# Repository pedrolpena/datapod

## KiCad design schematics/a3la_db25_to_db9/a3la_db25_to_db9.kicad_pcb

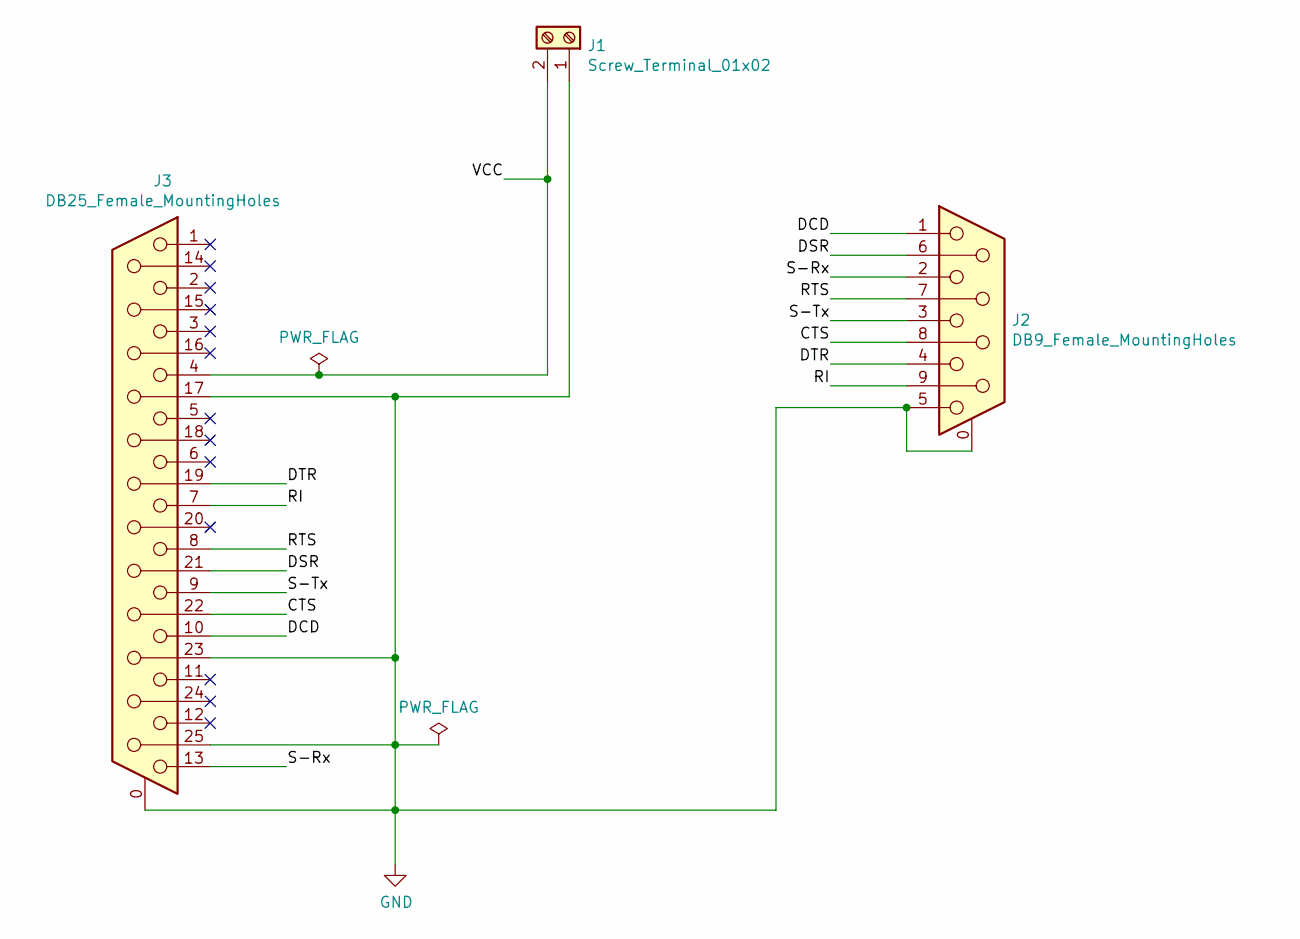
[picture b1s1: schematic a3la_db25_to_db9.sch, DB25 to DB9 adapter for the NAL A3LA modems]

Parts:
J1: Screw_Terminal_01x02; TerminalBlock_Phoenix_PT-1,5-2-5.0-H_1x02_P5.00mm_Horizontal; part# 277-1667-ND
J2: DB9_Female_MountingHoles; DSUB-9_Female_Horizontal_P2.77x2.84mm_EdgePinOffset7.70mm_H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; Part# A32075-ND
J3: DB25_Female_MountingHoles; DSUB-25_Female_Horizontal_P2.77x2.84mm_EdgePinOffset7.70mm_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; Part# A32077-ND

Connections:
/CTS: J2.8, J3.22
/DCD: J2.1, J3.10
/DSR: J2.6, J3.21
/DTR: J2.4, J3.19
/RI: J2.9, J3.7
/RTS: J2.7, J3.8
/S-Rx: J2.2, J3.13
/S-Tx: J2.3, J3.9
/VCC: J1.2, J3.4
GND: J1.1, J2.0 (PAD), J2.5, J3.0 (PAD), J3.17, J3.23, J3.25

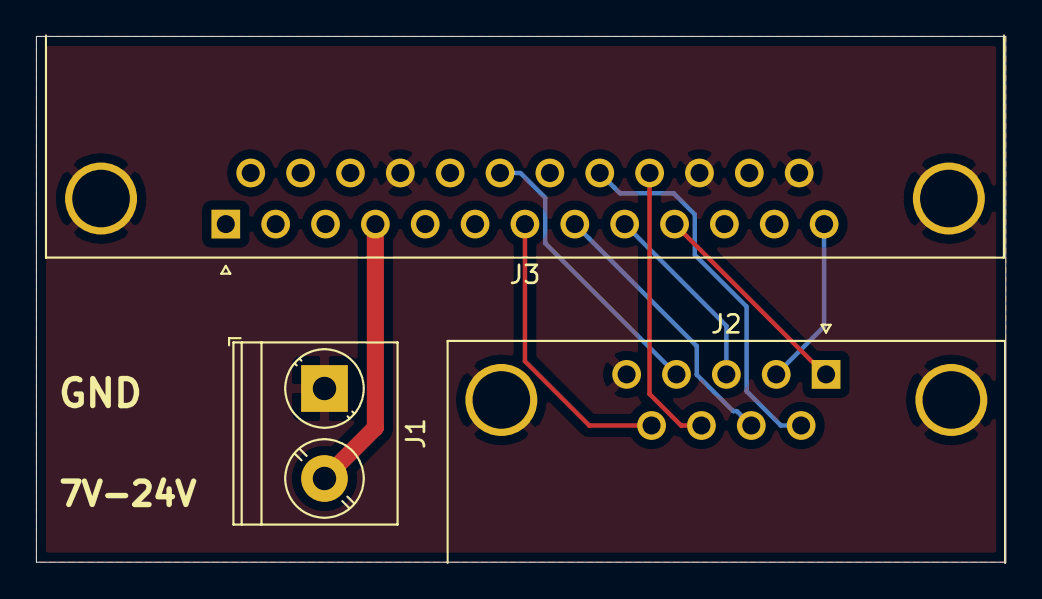
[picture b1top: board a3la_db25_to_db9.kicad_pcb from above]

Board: 2 copper layers, 53.8 x 29.2 mm, 3 parts (0 on the bottom side), 10 nets.

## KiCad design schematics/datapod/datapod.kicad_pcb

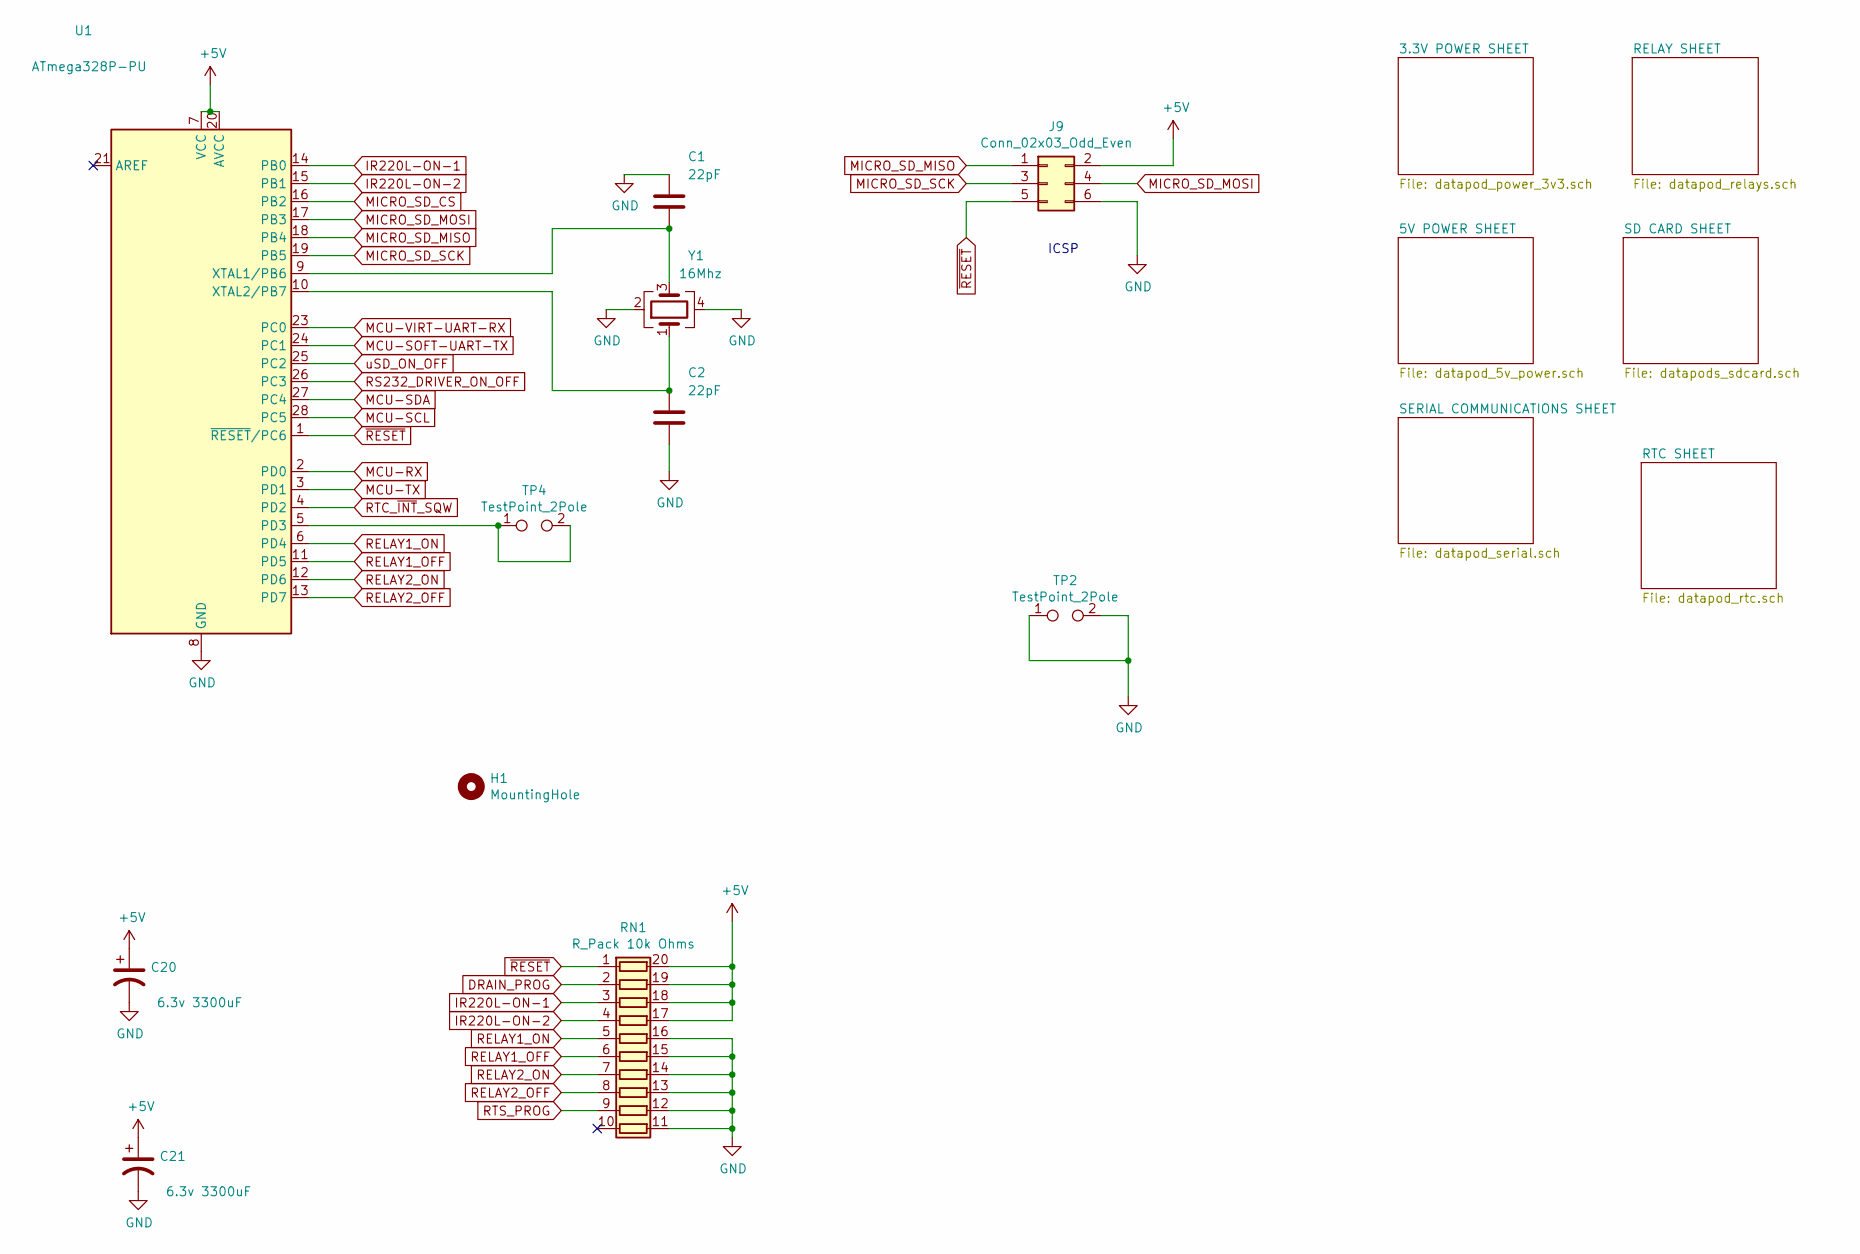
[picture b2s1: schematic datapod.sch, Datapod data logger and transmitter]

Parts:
C1, C2: 22pF; C_1206_3216Metric_Pad1.42x1.75mm_HandSolder; Part# 399-8165-1-ND
C20, C21: 6.3v 3300uF; CP_Radial_D10.0mm_P5.00mm; Part# 493-1009-ND
H1: MountingHole; MountingHole_0.4_inches_Pad_Via; Part# DNI
J9: Conn_02x03_Odd_Even; PinHeader_2x03_P2.54mm_Vertical_SMD; Part# WM17457-ND
RN1: R_Pack 10k Ohms; SSOP-20_3.9x8.7mm_P0.635mm; Part# OSOPT-10KACT-ND
TP2, TP4: TestPoint_2Pole; TestPoint_2Pads_Pitch5.08mm_Drill1.3mm; Part# DNI
U1: ATmega328P-PU; DIP-28_W7.62mm_SMDSocket_SmallPads; Part# 110-47-328-41-105000
Y1: 16Mhz; Oscillator_SMD_EuroQuartz_XO32-4Pin_3.2x2.5mm_HandSoldering; Part# 732-FA-23816B-C

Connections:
+5V: C20.1, C21.1, J9.2, RN1.17 (R4.2), RN1.18 (R3.2), RN1.19 (R2.2), RN1.20 (R1.2), U1.7 (VCC), U1.20 (AVCC); also elsewhere on the board
DRAIN_PROG: RN1.2 (R2.1); also elsewhere on the board
GND: C1.1, C2.2, C20.2, C21.2, J9.6, RN1.11 (R10.2), RN1.12 (R9.2), RN1.13 (R8.2), RN1.14 (R7.2), RN1.15 (R6.2), RN1.16 (R5.2), TP2.1, TP2.2, U1.8 (GND), U1.22 (GND), Y1.2, Y1.4; also elsewhere on the board
IR220L-ON-1: RN1.3 (R3.1), U1.14 (PB0); also elsewhere on the board
IR220L-ON-2: RN1.4 (R4.1), U1.15 (PB1); also elsewhere on the board
MCU-RX: U1.2 (PD0); also elsewhere on the board
MCU-SCL: U1.28 (PC5); also elsewhere on the board
MCU-SDA: U1.27 (PC4); also elsewhere on the board
MCU-SOFT-UART-TX: U1.24 (PC1); also elsewhere on the board
MCU-TX: U1.3 (PD1); also elsewhere on the board
MCU-VIRT-UART-RX: U1.23 (PC0); also elsewhere on the board
MICRO_SD_CS: U1.16 (PB2); also elsewhere on the board
MICRO_SD_MISO: J9.1, U1.18 (PB4); also elsewhere on the board
MICRO_SD_MOSI: J9.4, U1.17 (PB3); also elsewhere on the board
MICRO_SD_SCK: J9.3, U1.19 (PB5); also elsewhere on the board
unnamed: C1.2, U1.9 (XTAL1/PB6), Y1.3
unnamed: C2.1, U1.10 (XTAL2/PB7), Y1.1
unnamed: TP4.1, TP4.2, U1.5 (PD3)
RELAY1_OFF: RN1.6 (R6.1), U1.11 (PD5); also elsewhere on the board
RELAY1_ON: RN1.5 (R5.1), U1.6 (PD4); also elsewhere on the board
RELAY2_OFF: RN1.8 (R8.1), U1.13 (PD7); also elsewhere on the board
RELAY2_ON: RN1.7 (R7.1), U1.12 (PD6); also elsewhere on the board
RS232_DRIVER_ON_OFF: U1.26 (PC3); also elsewhere on the board
RTC_~INT~_SQW: U1.4 (PD2); also elsewhere on the board
RTS_PROG: RN1.9 (R9.1); also elsewhere on the board
uSD_ON_OFF: U1.25 (PC2); also elsewhere on the board
~RESET: J9.5, RN1.1 (R1.1), U1.1 (~RESET~/PC6); also elsewhere on the board

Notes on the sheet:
ICSP

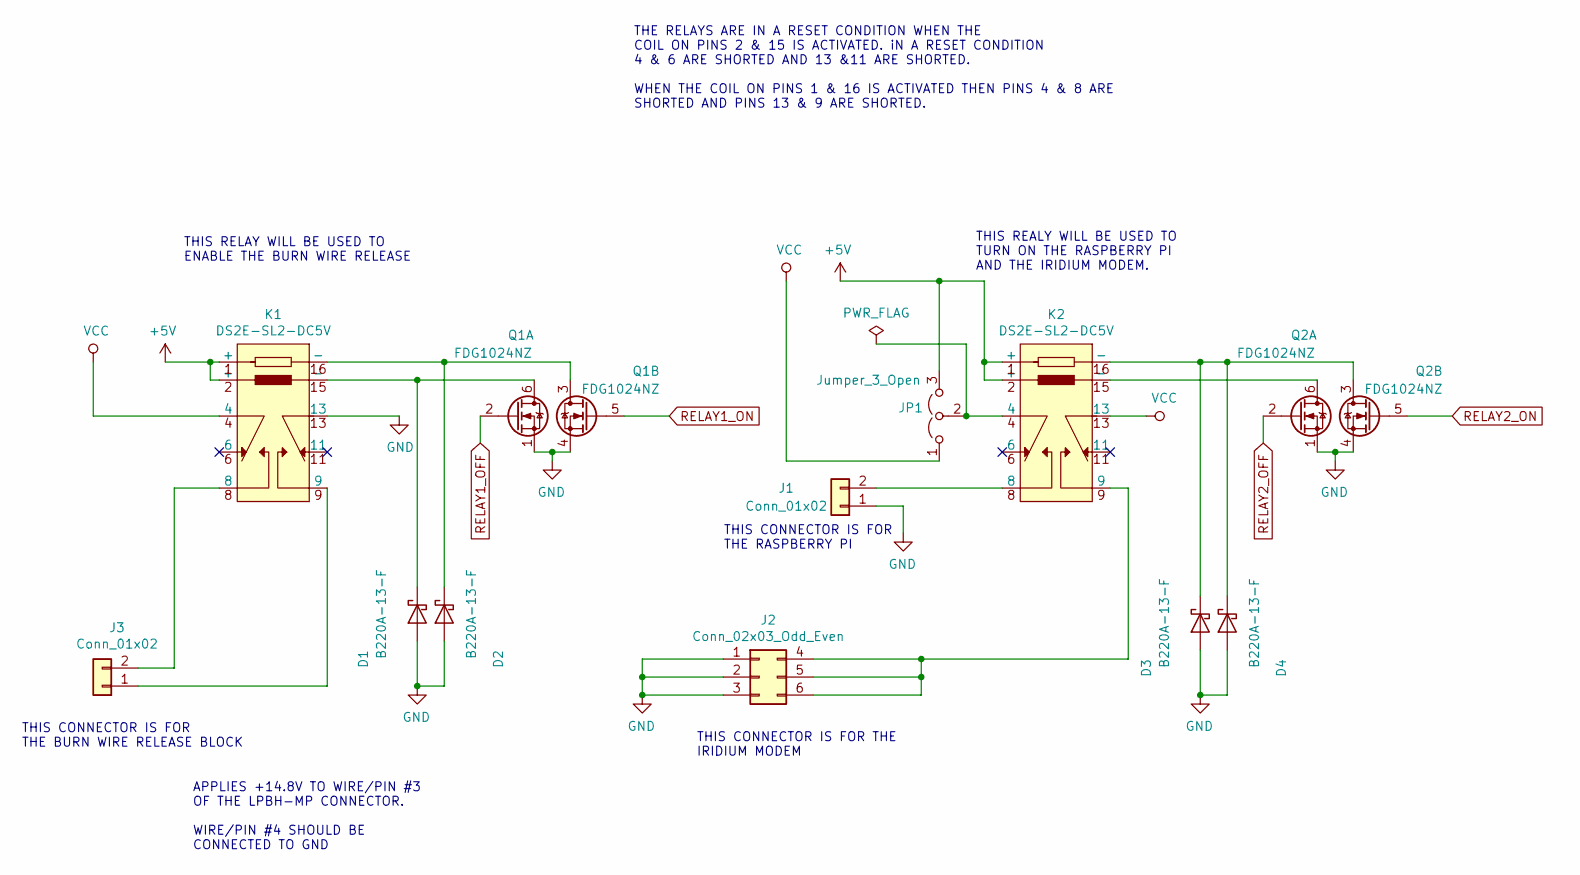
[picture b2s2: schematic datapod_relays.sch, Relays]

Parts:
D1, D2, D3, D4: B220A-13-F; D_SMA; Part# B220A-FDIDKR-ND
J1: Conn_01x02; Molex_Mini-Fit_Jr_5569-02A1_2x01_P4.20mm_Horizontal; Part# WM3900-ND
J2: Conn_02x03_Odd_Even; Molex_Mega-Fit_76825-0006_2x03_P5.70mm_Horizontal; Part# WM11971-ND
J3: Conn_01x02; Molex_Mega-Fit_76825-0002_2x01_P5.70mm_Horizontal; Part# WM11969-ND
JP1: Jumper_3_Open; SolderJumper-3_P1.3mm_Open_RoundedPad1.0x1.5mm
K1, K2: DS2E-SL2-DC5V; DIP-16_W7.62mm_SMDSocket_SmallPads; Part# ED11086-ND
Q1, Q2: FDG1024NZ; SOT-363_SC-70-6; Part# FDG1024NZFSCT-ND

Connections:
+5V: JP1.3 (B), K1.1 (+), K1.2 (+), K2.1 (+), K2.2 (+); also elsewhere on the board
GND: D1.2 (A), D2.2 (A), D3.2 (A), D4.2 (A), J1.1, J2.1, J2.2, J2.3, K1.13, Q1.1 (S), Q1.4 (S), Q2.1 (S), Q2.4 (S); also elsewhere on the board
unnamed: D1.1 (K), K1.15 (-), Q1.6 (D)
unnamed: D2.1 (K), K1.16 (-), Q1.3 (D)
unnamed: D3.1 (K), D4.1 (K), K2.16 (-), Q2.3 (D)
unnamed: J1.2, K2.8
unnamed: J2.4, J2.5, J2.6, K2.9
unnamed: J3.1, K1.9
unnamed: J3.2, K1.8
unnamed: JP1.2 (C), K2.4
unnamed: K2.15 (-), Q2.6 (D)
RELAY1_OFF: Q1.2 (G); also elsewhere on the board
RELAY1_ON: Q1.5 (G); also elsewhere on the board
RELAY2_OFF: Q2.2 (G); also elsewhere on the board
RELAY2_ON: Q2.5 (G); also elsewhere on the board

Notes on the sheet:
THE RELAYS ARE IN A RESET CONDITION WHEN THE COIL ON PINS 2 & 15 IS ACTIVATED. iN A RESET CONDITION 4 & 6 ARE SHORTED AND 13 &11 ARE SHORTED. WHEN THE COIL ON PINS 1 & 16 IS ACTIVATED THEN PINS 4 & 8 ARE SHORTED AND PINS 13 & 9 ARE SHORTED.
THIS RELAY WILL BE USED TO ENABLE THE BURN WIRE RELEASE
THIS REALY WILL BE USED TO TURN ON THE RASPBERRY PI AND THE IRIDIUM MODEM.
APPLIES +14.8V TO WIRE/PIN #3 OF THE LPBH-MP CONNECTOR. WIRE/PIN #4 SHOULD BE CONNECTED TO GND
THIS CONNECTOR IS FOR THE IRIDIUM MODEM
THIS CONNECTOR IS FOR THE BURN WIRE RELEASE BLOCK
THIS CONNECTOR IS FOR THE RASPBERRY PI

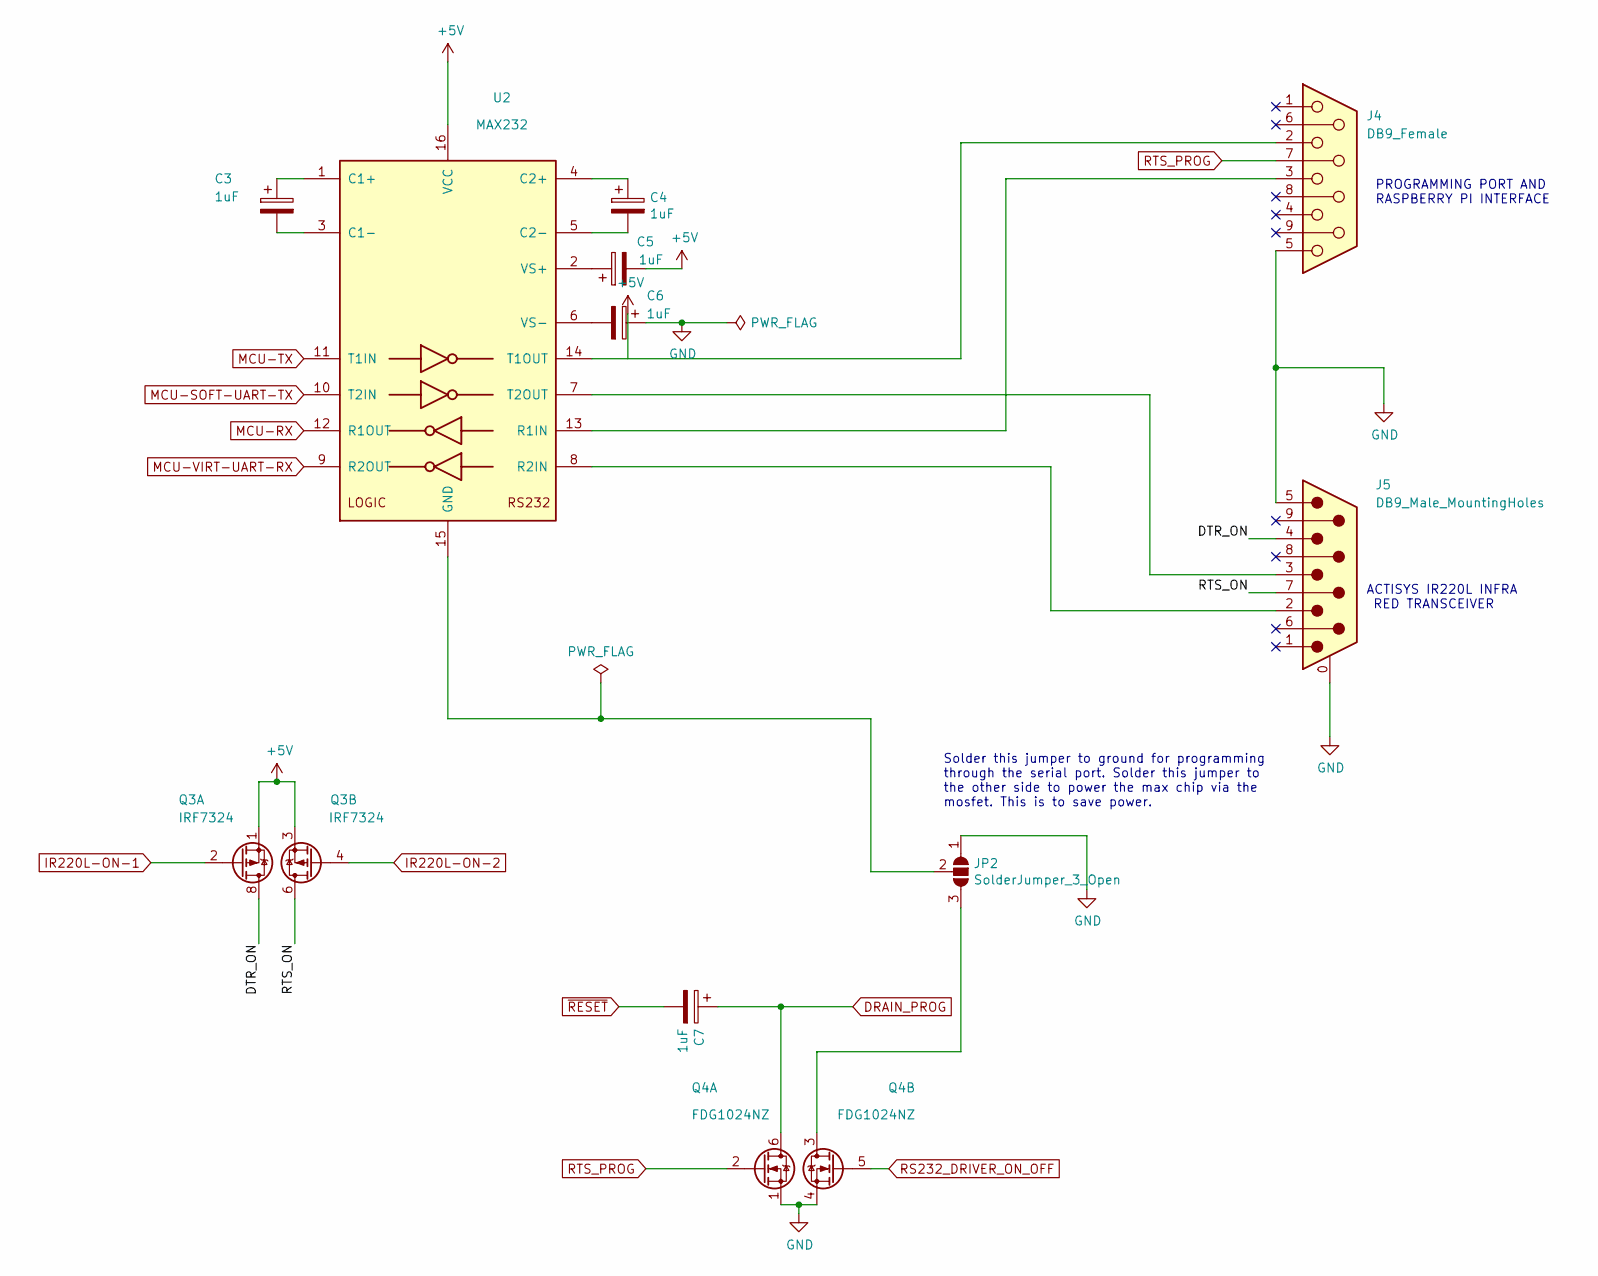
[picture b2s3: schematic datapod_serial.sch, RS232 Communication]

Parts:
C3, C4, C5, C6, C7: 1uF; C_0805_2012Metric_Pad1.15x1.40mm_HandSolder; Part# TCJP105M025R0500
J4: DB9_Female; DSUB-9_Female_Horizontal_P2.77x2.84mm_EdgePinOffset7.70mm_H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; Part# AE10921-ND
J5: DB9_Male_MountingHoles; DSUB-9_Male_Horizontal_P2.77x2.84mm_EdgePinOffset7.70mm_Hou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; Part# AE10968-ND
JP2: SolderJumper_3_Open; SolderJumper-3_P1.3mm_Open_RoundedPad1.0x1.5mm; Part# DNI
Q3: IRF7324; SOIC-8_3.9x4.9mm_P1.27mm; Part# IRF7324PBFTR-ND
Q4: FDG1024NZ; SOT-363_SC-70-6; Part# FDG1024NZFSCT-ND
U2: MAX232; SOIC-16_3.9x9.9mm_P1.27mm; Part# 296-14619-1-ND

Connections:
+5V: C5.2, Q3.1 (S1), Q3.3 (S2), U2.16 (VCC); also elsewhere on the board
/SERIAL COMMUNICATIONS SHEET/DTR_ON: J5.4, Q3.7 (D1), Q3.8 (D1)
/SERIAL COMMUNICATIONS SHEET/RTS_ON: J5.7, Q3.5 (D2), Q3.6 (D2)
DRAIN_PROG: C7.1, Q4.6 (D); also elsewhere on the board
GND: C6.1, J4.5, J5.0 (PAD), J5.5, JP2.1 (A), Q4.1 (S), Q4.4 (S); also elsewhere on the board
IR220L-ON-1: Q3.2 (G1); also elsewhere on the board
IR220L-ON-2: Q3.4 (G2); also elsewhere on the board
MCU-RX: U2.12 (R1OUT); also elsewhere on the board
MCU-SOFT-UART-TX: U2.10 (T2IN); also elsewhere on the board
MCU-TX: U2.11 (T1IN); also elsewhere on the board
MCU-VIRT-UART-RX: U2.9 (R2OUT); also elsewhere on the board
unnamed: C3.1, U2.1 (C1+)
unnamed: C3.2, U2.3 (C1-)
unnamed: C4.1, U2.4 (C2+)
unnamed: C4.2, U2.5 (C2-)
unnamed: C5.1, U2.2 (VS+)
unnamed: C6.2, U2.6 (VS-)
unnamed: J4.2, U2.14 (T1OUT)
unnamed: J4.3, U2.13 (R1IN)
unnamed: J5.2, U2.8 (R2IN)
unnamed: J5.3, U2.7 (T2OUT)
unnamed: JP2.2 (C), U2.15 (GND)
unnamed: JP2.3 (B), Q4.3 (D)
RS232_DRIVER_ON_OFF: Q4.5 (G); also elsewhere on the board
RTS_PROG: J4.7, Q4.2 (G); also elsewhere on the board
~RESET: C7.2; also elsewhere on the board

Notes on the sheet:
PROGRAMMING PORT AND RASPBERRY PI INTERFACE
ACTISYS IR220L INFRA RED TRANSCEIVER
Solder this jumper to ground for programming through the serial port. Solder this jumper to the other side to power the max chip via the mosfet. This is to save power.

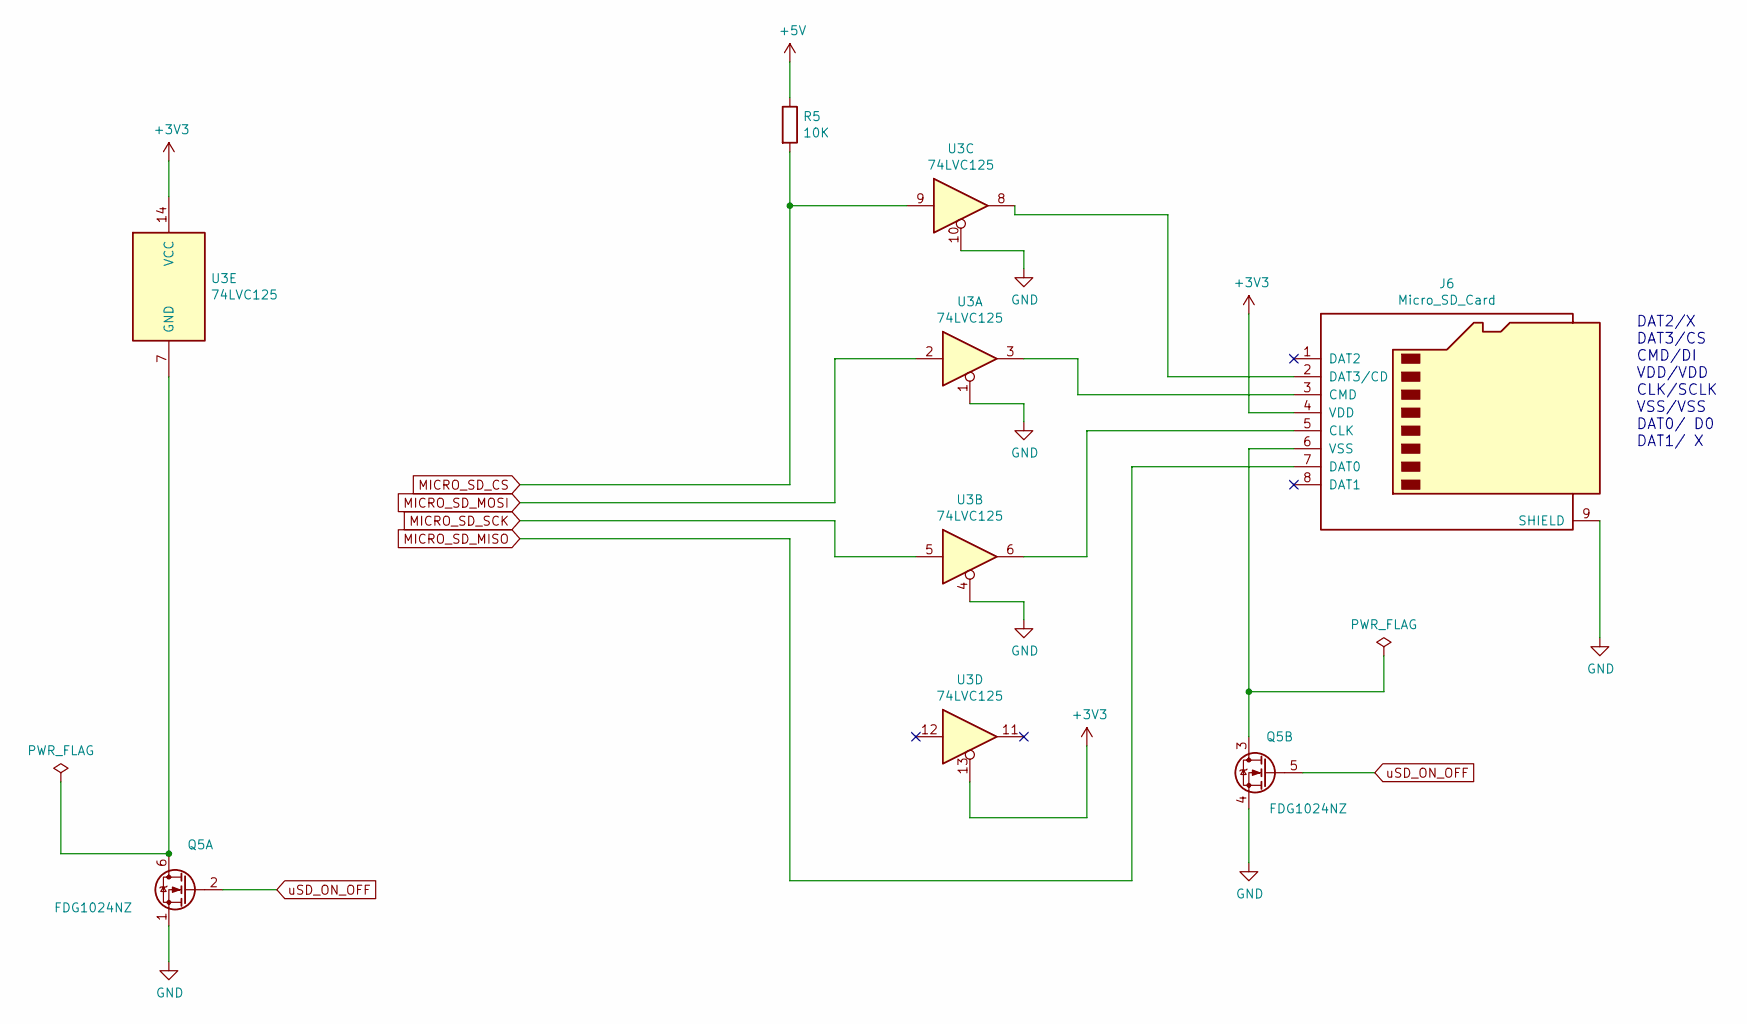
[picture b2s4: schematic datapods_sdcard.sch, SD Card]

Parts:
J6: Micro_SD_Card; microSD_HC_Wuerth_693072010801; Part# 732-3820-1-ND
Q5: FDG1024NZ; SOT-363_SC-70-6; Part# FDG1024NZFSCT-ND
R5: 10K; R_1206_3216Metric_Pad1.42x1.75mm_HandSolder; Part# 311-10KERCT-ND
U3: 74LVC125; TSSOP-14_4.4x5mm_P0.65mm; Part# 296-1222-1-ND

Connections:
+3V3: J6.4 (VDD), U3.13, U3.14 (VCC); also elsewhere on the board
+5V: R5.1; also elsewhere on the board
GND: J6.9 (SHIELD), Q5.1 (S), Q5.4 (S), U3.1, U3.4, U3.10; also elsewhere on the board
MICRO_SD_CS: R5.2, U3.9; also elsewhere on the board
MICRO_SD_MISO: J6.7 (DAT0); also elsewhere on the board
MICRO_SD_MOSI: U3.2; also elsewhere on the board
MICRO_SD_SCK: U3.5; also elsewhere on the board
unnamed: J6.2 (DAT3/CD), U3.8
unnamed: J6.3 (CMD), U3.3
unnamed: J6.5 (CLK), U3.6
unnamed: J6.6 (VSS), Q5.3 (D)
unnamed: Q5.6 (D), U3.7 (GND)
uSD_ON_OFF: Q5.2 (G), Q5.5 (G); also elsewhere on the board

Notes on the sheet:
DAT2/X DAT3/CS CMD/DI VDD/VDD CLK/SCLK VSS/VSS DAT0/ D0 DAT1/ X

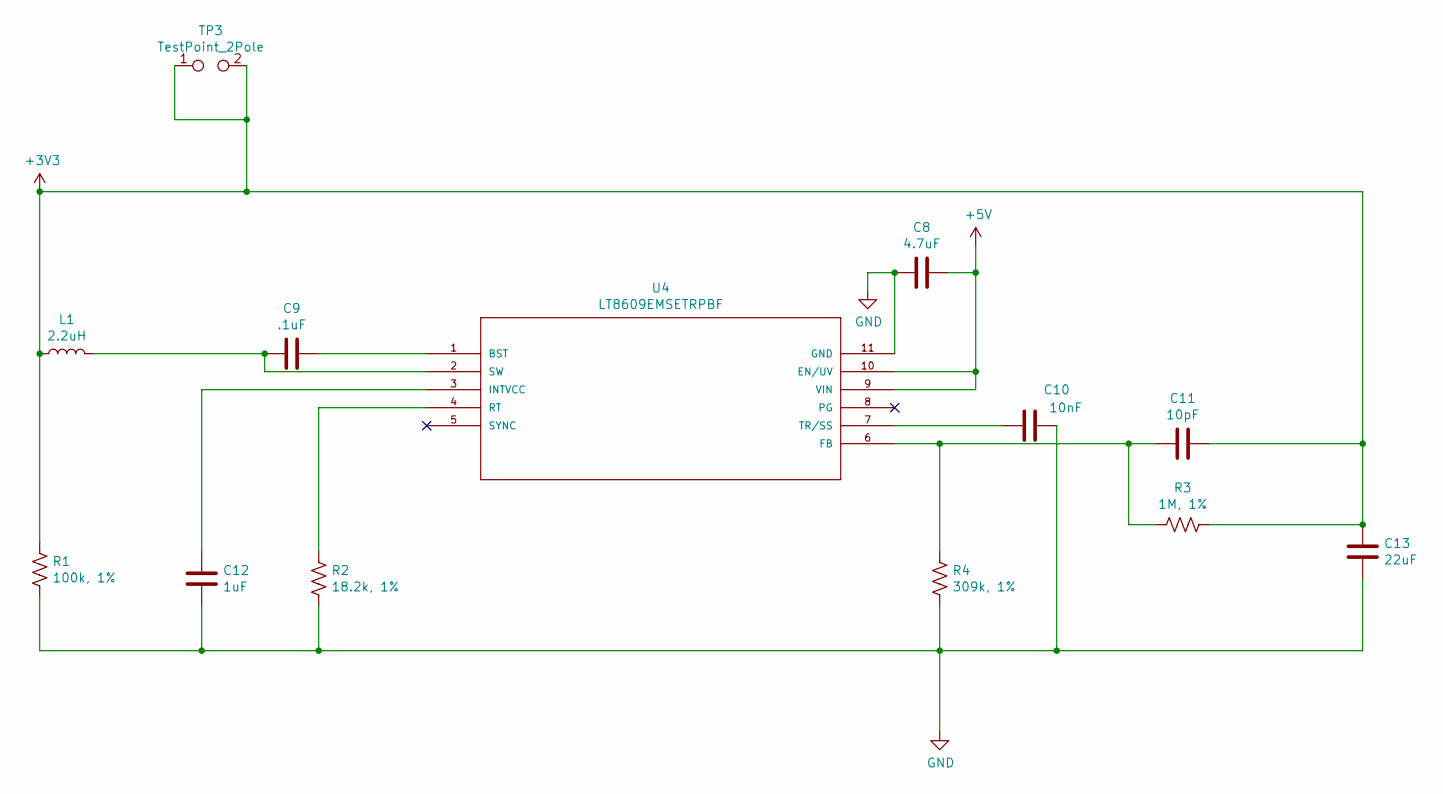
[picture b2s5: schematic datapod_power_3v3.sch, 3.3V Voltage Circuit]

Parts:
C8: 4.7uF; C_0805_2012Metric_Pad1.15x1.40mm_HandSolder; Part# 490-12753-1-ND
C9: .1uF; C_0805_2012Metric_Pad1.15x1.40mm_HandSolder; Part# 478-3351-1-ND
C10: 10nF; C_0805_2012Metric_Pad1.15x1.40mm_HandSolder; Part# 311-1136-1-ND
C11: 10pF; C_0805_2012Metric_Pad1.15x1.40mm_HandSolder; Part# 399-7062-1-ND
C12: 1uF; C_0805_2012Metric_Pad1.15x1.40mm_HandSolder; Part# 311-1365-1-ND
C13: 22uF; C_0805_2012Metric_Pad1.15x1.40mm_HandSolder; Part# 1276-6780-1-ND
L1: 2.2uH; L_0805_2012Metric_Pad1.15x1.40mm_HandSolder; Part# 587-2771-1-ND
R1: 100k, 1%; R_0805_2012Metric_Pad1.15x1.40mm_HandSolder; Part# 311-100KCRCT-ND
R2: 18.2k, 1%; R_0805_2012Metric_Pad1.15x1.40mm_HandSolder; Part# 311-18.2KCRCT-ND
R3: 1M, 1%; R_0805_2012Metric_Pad1.15x1.40mm_HandSolder; Part# 311-1.00MCRCT-ND
R4: 309k, 1%; R_0805_2012Metric_Pad1.15x1.40mm_HandSolder; Part# 311-309KCRCT-ND
TP3: TestPoint_2Pole; TestPoint_2Pads_Pitch5.08mm_Drill1.3mm
U4: LT8609EMSETRPBF; MSOP-10-1EP_3x3mm_P0.5mm_EP1.73x1.98mm; Part# LT8609EMSE#TRPBFCT-ND

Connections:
+3V3: C11.2, C13.1, L1.1, R1.1, R3.1, TP3.1, TP3.2; also elsewhere on the board
+5V: C8.1, U4.9 (VIN), U4.10 (EN/UV); also elsewhere on the board
GND: C8.2, C10.1, C12.2, C13.2, R1.2, R2.2, R4.2, U4.11 (GND); also elsewhere on the board
unnamed: C9.1, U4.1 (BST)
unnamed: C9.2, L1.2, U4.2 (SW)
unnamed: C10.2, U4.7 (TR/SS)
unnamed: C11.1, R3.2, R4.1, U4.6 (FB)
unnamed: C12.1, U4.3 (INTVCC)
unnamed: R2.1, U4.4 (RT)

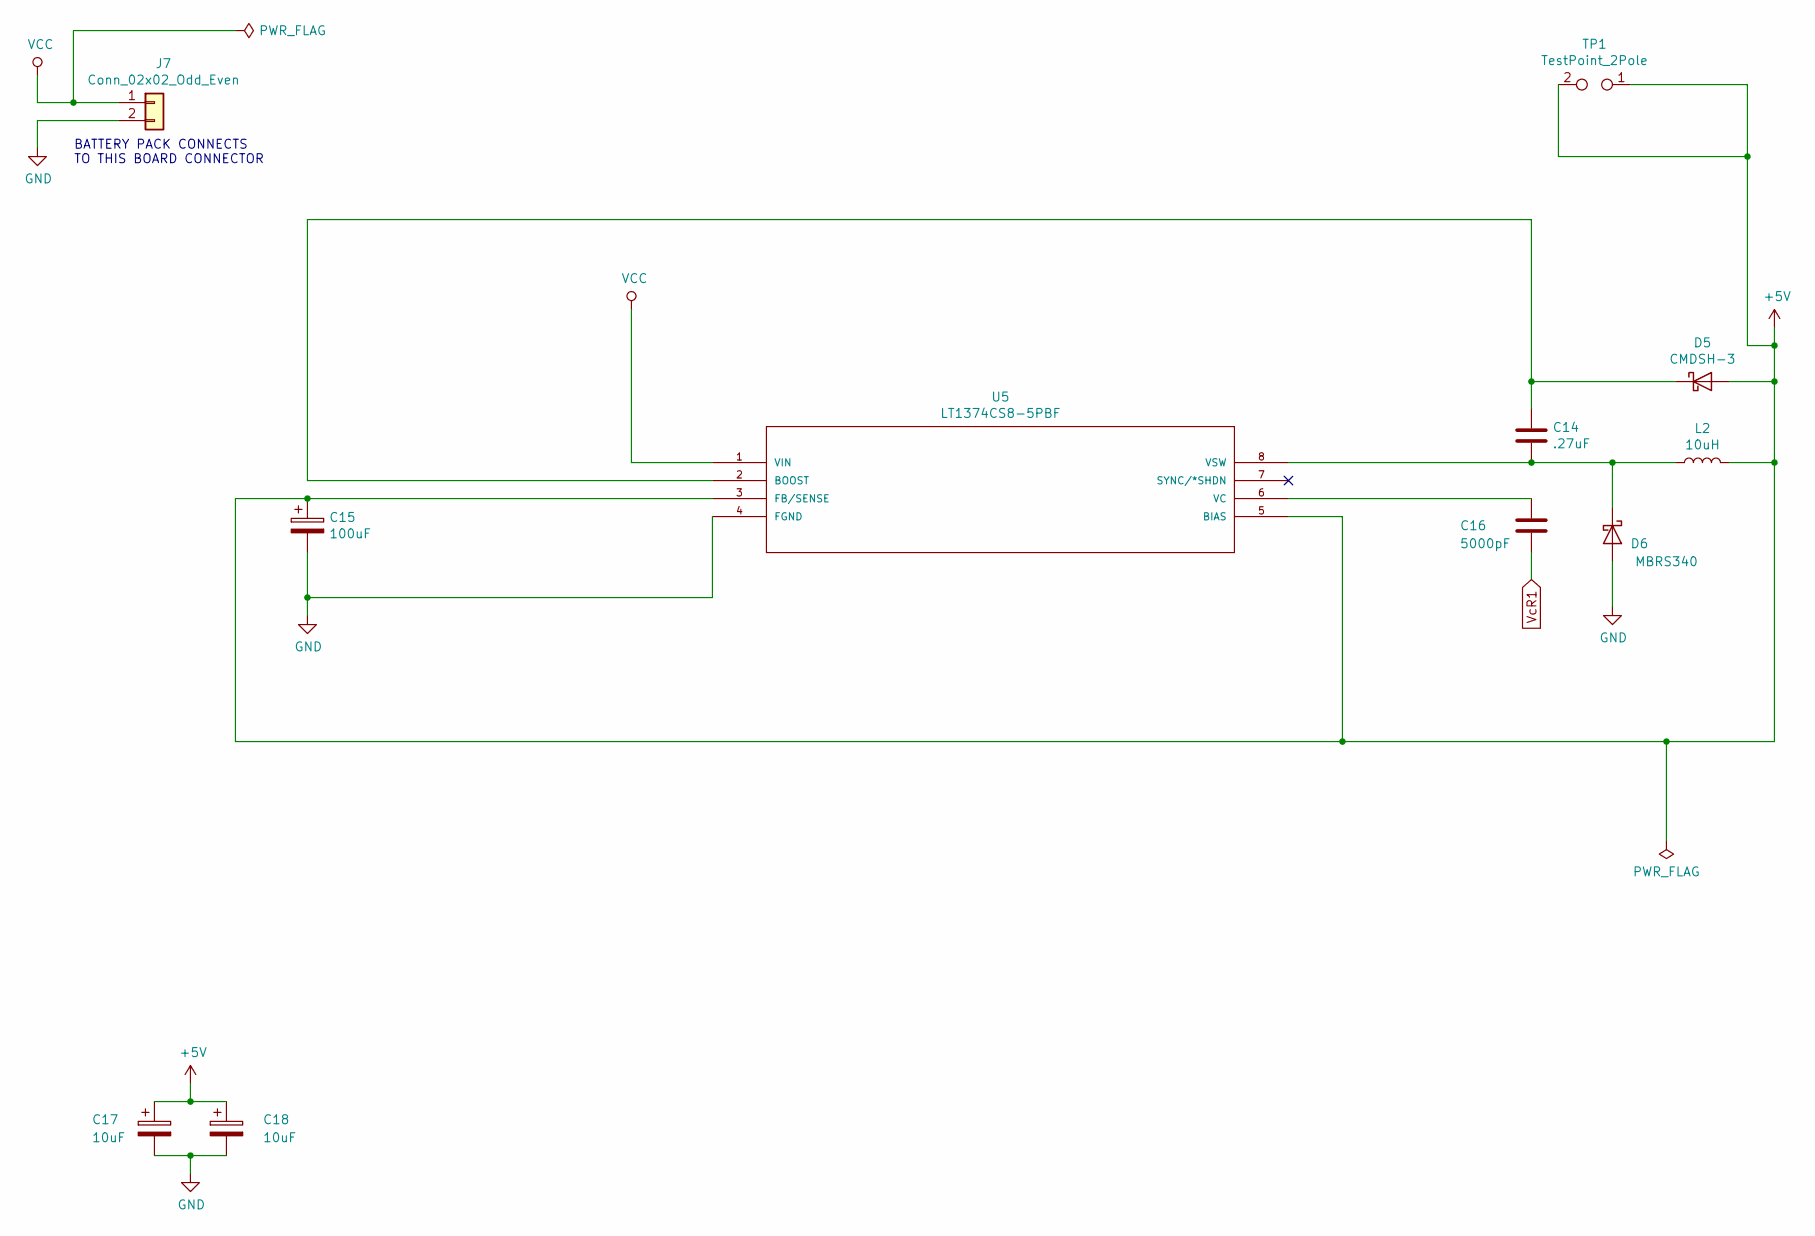
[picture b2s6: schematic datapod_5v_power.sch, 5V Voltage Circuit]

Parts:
C14: .27uF; C_1206_3216Metric_Pad1.42x1.75mm_HandSolder; Part# 478-1561-1-ND
C15: 100uF; CP_EIA-7343-31_Kemet-D_Pad2.25x2.55mm_HandSolder; Part# 718-1890-1-ND
C16: 5000pF; C_0805_2012Metric_Pad1.15x1.40mm_HandSolder; Part# 478-10560-1-ND
C17, C18: 10uF; C_1206_3216Metric_Pad1.42x1.75mm_HandSolder; Part# TCJA106M025R0150
D5: CMDSH-3; D_SOD-323_HandSoldering; Part# 1514-CMDSH-3TRPBFREECT-ND
D6: MBRS340; D_SMC; Part# MBRS340FSCT-ND
J7: Conn_02x02_Odd_Even; Molex_Nano-Fit_105309-xx02_1x02_P2.50mm_Vertical; Part# WM15036-ND
L2: 10uH; L_Sumida_CDMC6D28_7.25x6.5mm; Part# SRP6540-100MCT-ND
TP1: TestPoint_2Pole; TestPoint_2Pads_Pitch5.08mm_Drill1.3mm; Part# DNI
U5: LT1374CS8-5PBF; SO-8_3.9x4.9mm_P1.27mm; Part# LT1374CS8-5#PBF-ND

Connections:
+5V: C15.1, C17.1, C18.1, D5.2 (A), L2.2, TP1.1, TP1.2, U5.3 (FB/SENSE), U5.5 (BIAS); also elsewhere on the board
GND: C15.2, C17.2, C18.2, D6.2 (A), J7.2, U5.4 (FGND); also elsewhere on the board
unnamed: C14.1, D5.1 (K), U5.2 (BOOST)
unnamed: C14.2, D6.1 (K), L2.1, U5.8 (VSW)
unnamed: C16.1, U5.6 (VC)
VcR1: C16.2; also elsewhere on the board

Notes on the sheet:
BATTERY PACK CONNECTS TO THIS BOARD CONNECTOR

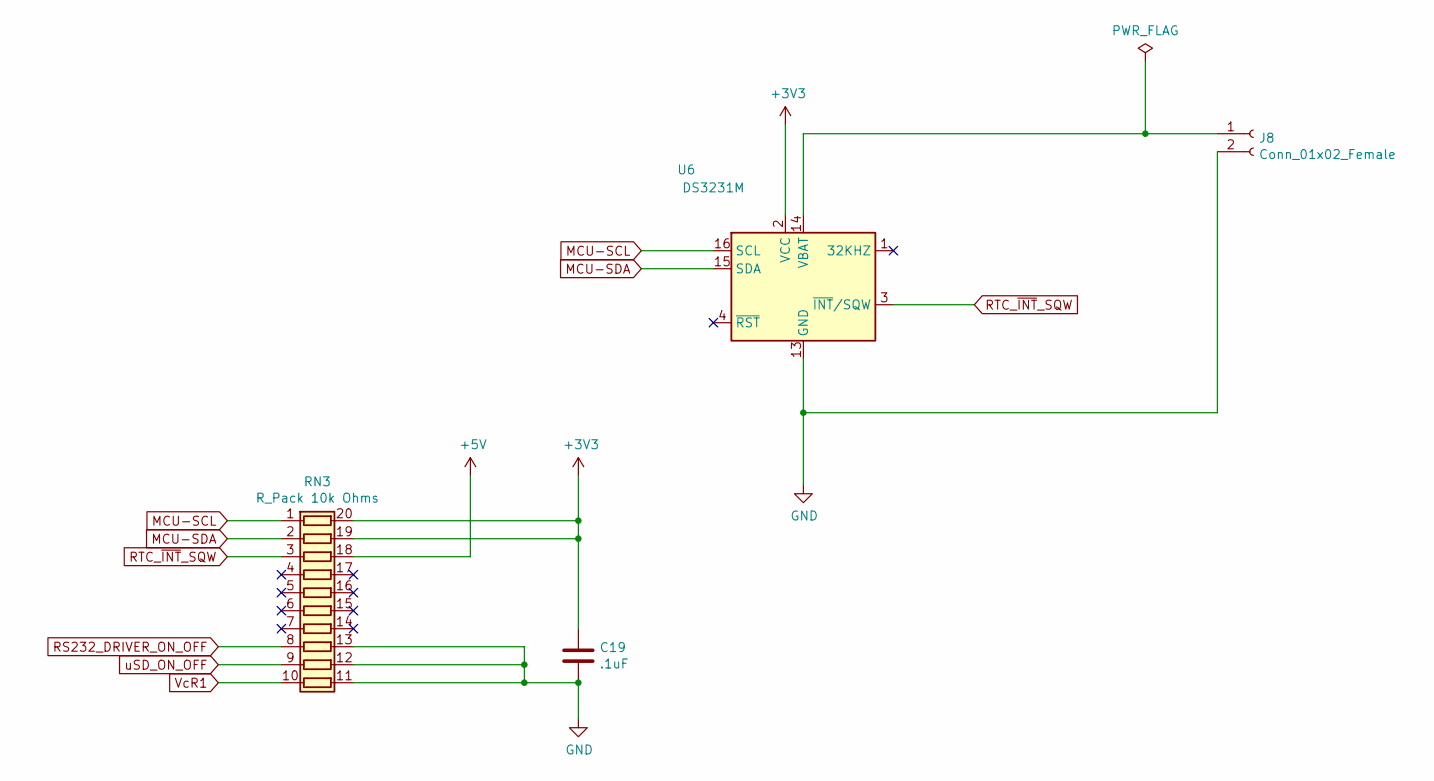
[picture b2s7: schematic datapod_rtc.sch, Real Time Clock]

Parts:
C19: .1uF; C_0805_2012Metric_Pad1.15x1.40mm_HandSolder; Part# 478-3351-1-ND
J8: Conn_01x02_Female; BatteryHolder_Keystone_1058_1x2032; Part# 36-1058CT-ND
RN3: R_Pack 10k Ohms; SSOP-20_3.9x8.7mm_P0.635mm; Part# OSOPT-10KACT-ND
U6: DS3231M; SOIC-16W_7.5x10.3mm_P1.27mm; Part# DS3231S#T&RCT-ND

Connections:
+3V3: C19.2, RN3.19 (R2.2), RN3.20 (R1.2), U6.2 (VCC); also elsewhere on the board
+5V: RN3.18 (R3.2); also elsewhere on the board
GND: C19.1, J8.2, RN3.11 (R10.2), RN3.12 (R9.2), RN3.13 (R8.2), U6.5 (GND), U6.6 (GND), U6.7 (GND), U6.8 (GND), U6.9 (GND), U6.10 (GND), U6.11 (GND), U6.12 (GND), U6.13 (GND); also elsewhere on the board
MCU-SCL: RN3.1 (R1.1), U6.16 (SCL); also elsewhere on the board
MCU-SDA: RN3.2 (R2.1), U6.15 (SDA); also elsewhere on the board
unnamed: J8.1, U6.14 (VBAT)
RS232_DRIVER_ON_OFF: RN3.8 (R8.1); also elsewhere on the board
RTC_~INT~_SQW: RN3.3 (R3.1), U6.3 (~INT~/SQW); also elsewhere on the board
VcR1: RN3.10 (R10.1); also elsewhere on the board
uSD_ON_OFF: RN3.9 (R9.1); also elsewhere on the board

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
